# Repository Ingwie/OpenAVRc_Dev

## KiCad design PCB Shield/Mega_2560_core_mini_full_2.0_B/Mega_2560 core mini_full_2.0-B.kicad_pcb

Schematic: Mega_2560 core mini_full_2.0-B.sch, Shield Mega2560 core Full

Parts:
C1, C2, C3, C5: 47nF; C_1206
C4, C6, C7, C9, C11, C16, C17, C26, C27, C29, C31, C32, C33, C34, C38: 100nF; C_1206
C28: 47µF; CP_Elec_6.3x5.3
C42: 6.8nF; C_1206
C43, C44, C45, C46: 4.7nF; C_1206
D1, D2, D6: MBR0520; D_SOD-123
P1: 2560-core; Connectors-2560-core
P2: Clock; Pin_Header_Straight_1x04_Pitch2.54mm
P3: Option; Pin_Header_Straight_1x04_Pitch2.54mm
P4: Potentiometre; Pin_Header_Straight_2x05_Pitch2.54mm
P5: Vibreur; Pin_Header_Straight_1x02_Pitch2.54mm
P6: Micro_sd; Pin_Header_Straight_1x06_Pitch2.54mm
P7: Option; Pin_Header_Straight_1x06_Pitch2.54mm
P8: Audio; Pin_Header_Straight_1x05_Pitch2.54mm
P9: SPI; Pin_Header_Straight_2x03_Pitch2.54mm
P10: SPI_libre; Pin_Header_Straight_1x03_Pitch2.54mm
P11: Trim; Pin_Header_Straight_2x05_Pitch2.54mm
P12: Stick_left; Pin_Header_Straight_1x04_Pitch2.54mm
P13: Stick_right; Pin_Header_Straight_1x04_Pitch2.54mm
P14: Switch; Pin_Header_Straight_2x05_Pitch2.54mm
P15: LCD_I2C; Pin_Header_Straight_1x04_Pitch2.54mm
P16: LCD; Pin_Header_Straight_2x10_Pitch2.54mm
P17: Battery LIPO; Pin_Header_Straight_1x02_Pitch2.54mm
P18: Ecolage; Pin_Header_Straight_1x02_Pitch2.54mm
P19: Module_TX; Pin_Header_Straight_2x04_Pitch2.54mm
P20: Module_RS232/TTL; Con_RS232_TTL
P21: Sw_power; Pin_Header_Straight_1x02_Pitch2.54mm
P22: CONN_JQ6500_28P_mini; connector_mini-JQ6500-28P
P23: Rot_1; Pin_Header_Straight_1x04_Pitch2.54mm
P24: Rot_2; Pin_Header_Straight_1x04_Pitch2.54mm
P25: Key_select_menu_ESC; Pin_Header_Straight_2x04_Pitch2.54mm
P26: LCD_Vcc_select; Pin_Header_Straight_1x03_Pitch2.54mm
R1, R2: 22K; R_1206
R3: 18K; R_1206
R4: 1K; R_1206
R5, R6: 10K; R_1206
R7: 500; R_1206
R8: 200; R_1206
R9: 220; R_1206
R11, R12, R13, R14: 100K; R_1206
R16: 2.7K; R_1206
R17: 5.1K; R_1206
R18, R19, R22, R23: 5.1k; R_1206
R24, R25: 33K; R_1206
R26, R29, R32, R35: 47K; R_1206
R27, R30, R33, R36: POT_100k; Potentiometer_Trimmer_Bourns_3296W
R28, R31, R34, R37: 270K; R_1206
RV1: 200K; Potentiometer_Triwood_RM-065
RV2, RV3, RV4, RV5: POT_100k; Potentiometer_Bourns_3296W_3-8Zoll_Inline_ScrewUp
RV6: 120; Potentiometer_Trimmer_Bourns_3266W
SW1: Inter_HF
SW3: Power switch
U1: 4066; SOP14
U2, U3: TLP290; SOP4
U4: L4941; TO-220
U5: LD1117S33TR; SOT-223
U6: MCP604-I/SL; SOP14
W1, W2, W3, W4: TEST_2P; TESTPT

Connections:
+BATT: D6.2 (A), P19.1, P21.1, R7.1, R17.2
/Isp_rst: P1.RESE (P75), P9.5
/Key_DOWN: P1.49 (P29), P25.4
/Key_ESC: P1.44 (P34), P25.7
/Key_LEFT: P1.46 (P32), P25.5
/Key_MENU: P1.45 (P33), P25.8
/Key_RIGHT: P1.47 (P31), P25.6
/Key_UP: P1.48 (P30), P25.3
/LCD_VCC: P15.2, P16.3, P26.2
/Lcd_A0: P1.D32 (P85), P16.16
/Lcd_bla: P1.D35 (P88), RV6.1
/Lcd_cs: P1.D34 (P87), P16.20
/Lcd_db0: P1.D22 (P74), P16.6
/Lcd_db1: P1.D23 (P71), P16.7
/Lcd_db2: P1.D24 (P72), P16.8
/Lcd_db3: P1.D25 (P69), P16.9
/Lcd_db4: P1.D26 (P70), P16.10
/Lcd_db5: P1.D27 (P67), P16.11
/Lcd_db6: P1.D28 (P68), P16.12
/Lcd_db7: P1.D29 (P65), P16.13
/Lcd_e: P1.D30 (P83), P16.14
/Lcd_r/w: P1.D31 (P84), P16.15
/Lcd_rst: P1.D33 (P86), P16.17
/Lcd_vo: P16.4, RV1.2
/Microsd_CS: P1.53 (P24), P6.1, P7.1
/Miso: P1.MISO (P79), P6.4, P7.4, P9.1
/Mosi: P1.MOSI (P78), P6.3, P7.3, P9.4
/PH2: P1.PH2 (P19), P10.1
/PPM_TX_OUT: D2.1 (K), P19.4
/PPM_in: P1.PE7 (P10), U1.11 (I/O)
/PPM_out: D2.2 (A), P1.PW12 (P27), U1.8 (I/O)
/Pot_1: P1.A12 (P55), P4.6
/Pot_2: P1.A13 (P58), P4.2
/Pot_3: P1.A14 (P57), P4.4
/RXD2: P1.D17 (P14), P10.3
/Rot_1A: C29.1, P1.PWD2 (P7), P23.3
/Rot_1B: C27.1, P1.PWD3 (P8), P23.2, R18.2
/Rot_1push: C26.1, P1.D15 (P12), P23.1, R19.2
/Rot_2A: C34.1, P1.D19 (P16), P24.3
/Rot_2B: C33.1, P1.D18 (P15), P24.2, R22.2
/Rot_2push: C32.1, P1.D14 (P11), P24.1, R23.2
/Sck: P1.SCK (P77), P6.2, P7.2, P9.3
/Scl: P1.D21 (P18), P2.1, P3.1, P15.4
/Sda: P1.D20 (P17), P2.2, P3.2, P15.3
/Sim_control: P1.PW11 (P26), U1.5 (ON), U1.13 (ON)
/Stick_LH: C45.1, P1.A11 (P56), R33.2, R33.3, U6.8, W3.1
/Stick_LHcon: C9.2, P12.2, R32.2, W3.2
/Stick_LV: C46.1, P1.A9 (P54), R36.2, R36.3, U6.14, W4.1
/Stick_LVcon: C11.2, P12.3, R35.2, W4.2
/Stick_RH: C43.1, P1.A8 (P51), R27.2, R27.3, U6.1, W1.1
/Stick_RHcon: C16.2, P13.2, R26.2, W1.2
/Stick_RV: C44.1, P1.A10 (P53), R30.2, R30.3, U6.7, W2.1
/Stick_RVcon: C17.2, P13.3, R29.2, W2.2
/Sw_ailDR: P1.D38 (P93), P14.5
/Sw_eleDR: P1.43 (P35), P14.7
/Sw_gear: P1.D40 (P91), P14.4
/Sw_id1: P1.D37 (P90), P14.1
/Sw_id2: P1.D36 (P89), P14.2
/Sw_rudDR: P1.D41 (P92), P14.3
/Sw_thcut: P1.D39 (P66), P14.6
/Sw_turn: P1.42 (P36), P14.8
/TXD2: P1.D16 (P13), P10.2
/Tele_RX: P1.RXD (P4), U3.3
/Tele_TX: P1.TXD (P5), U2.4
/Trim_LH->: P1.A6 (P49), P11.1
/Trim_LH<-: P1.A7 (P52), P11.2
/Trim_LV->: P1.A4 (P47), P11.7
/Trim_LV<-: P1.A5 (P50), P11.4
/Trim_RH->: P1.A0 (P43), P11.5
/Trim_RH<-: P1.A1 (P46), P11.6
/Trim_RV->: P1.A2 (P45), P11.8
/Trim_RV<-: P1.A3 (P48), P11.3
/U_batt: P1.A15 (P60), R16.2, R17.1
/Vibreur: P1.PJ7 (P73), R9.2
/audio_left_in: P1.PWD6 (P20), R1.2
/audio_right_in: P22.DACL (P16), R2.2
/core_pw10: P1.PW10 (P25), R3.1
/core_pw13: P1.PW13 (P28), R4.1
unnamed: C28.1, D6.1 (K), U4.1 (IN)
unnamed 79: C38.1, P26.1, U5.2 (VO); also elsewhere on the board
unnamed: C42.1, R24.2, R25.1, U6.3 (+), U6.5 (+), U6.10 (+), U6.12 (+)
unnamed: C43.2, R11.2, R26.1, R28.1, U6.2 (-)
unnamed: C44.2, R12.2, R29.1, R31.1, U6.6 (-)
unnamed: C45.2, R13.2, R32.1, R34.1, U6.9 (-)
unnamed: C46.2, R14.2, R35.1, R37.1, U6.13 (-)
unnamed: D1.1 (K), P5.1, R9.1
unnamed: P8.1, R1.1
unnamed: P8.2, R2.1
unnamed: P16.5, RV1.3
unnamed: P16.18, RV6.2
unnamed: P17.2, P21.2
unnamed: P18.1, R8.1
unnamed: P19.2, P19.3
unnamed: P20.3, U2.3
unnamed: P22.BUSY (P20), R3.2
unnamed: P22.RX (P18), R4.2
unnamed: R5.2, U1.2 (O/I), U1.6 (ON)
unnamed: R6.2, U1.3 (O/I), U1.12 (ON)
unnamed: R7.2, U2.1, U3.1
unnamed: R8.2, U1.9 (O/I), U1.10 (O/I)
unnamed: R11.1, R27.1
unnamed: R12.1, R30.1
unnamed: R13.1, R33.1
unnamed: R14.1, R36.1
unnamed: R28.2, RV2.2
unnamed: R31.2, RV3.2
unnamed: R34.2, RV4.2
unnamed: R37.2, RV5.2

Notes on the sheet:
+3.3V
+5V
Isolation Module TTL
Power Management
PPM Management
Stick control
Option si utilisation du 3.3V dans le montage
Option Amplification des sticks (Fonctionne sans)
Option si utilisation de la télémètrie
Alim module

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
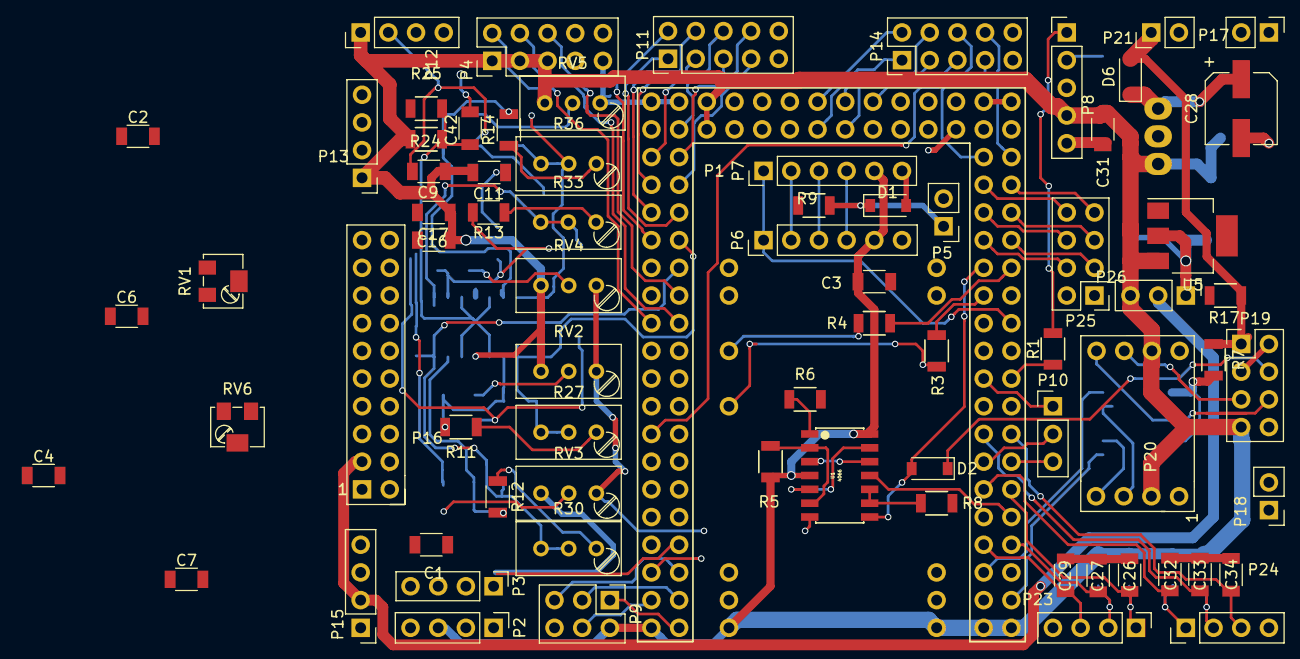
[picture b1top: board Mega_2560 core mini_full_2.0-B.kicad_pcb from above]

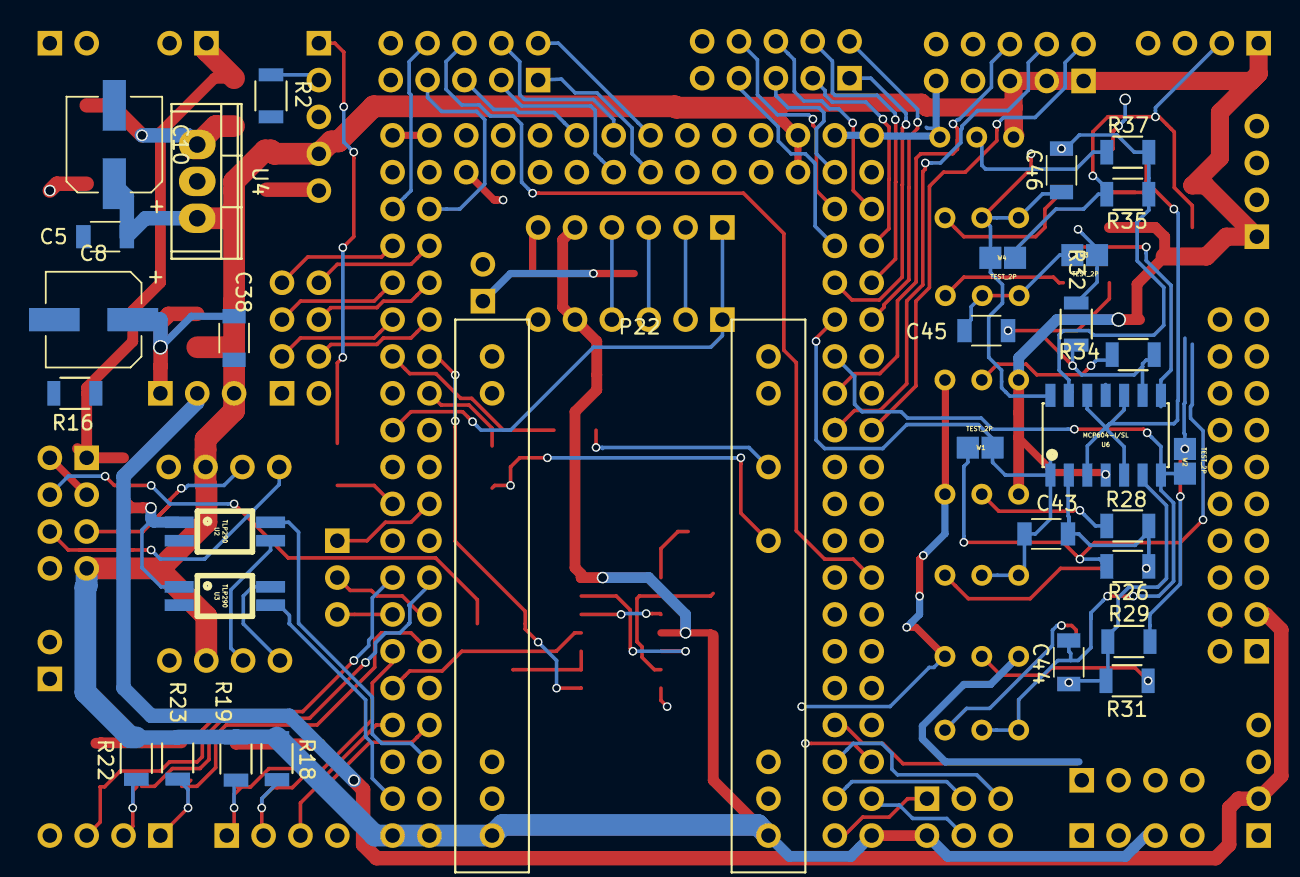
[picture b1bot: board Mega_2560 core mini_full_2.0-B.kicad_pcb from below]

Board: 2 copper layers, 105 parts (31 on the bottom side), 113 nets.

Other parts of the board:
C8, C10: 47µF; CP_Elec_6.3x5.3

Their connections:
unnamed 79: C8.1; also elsewhere on the board

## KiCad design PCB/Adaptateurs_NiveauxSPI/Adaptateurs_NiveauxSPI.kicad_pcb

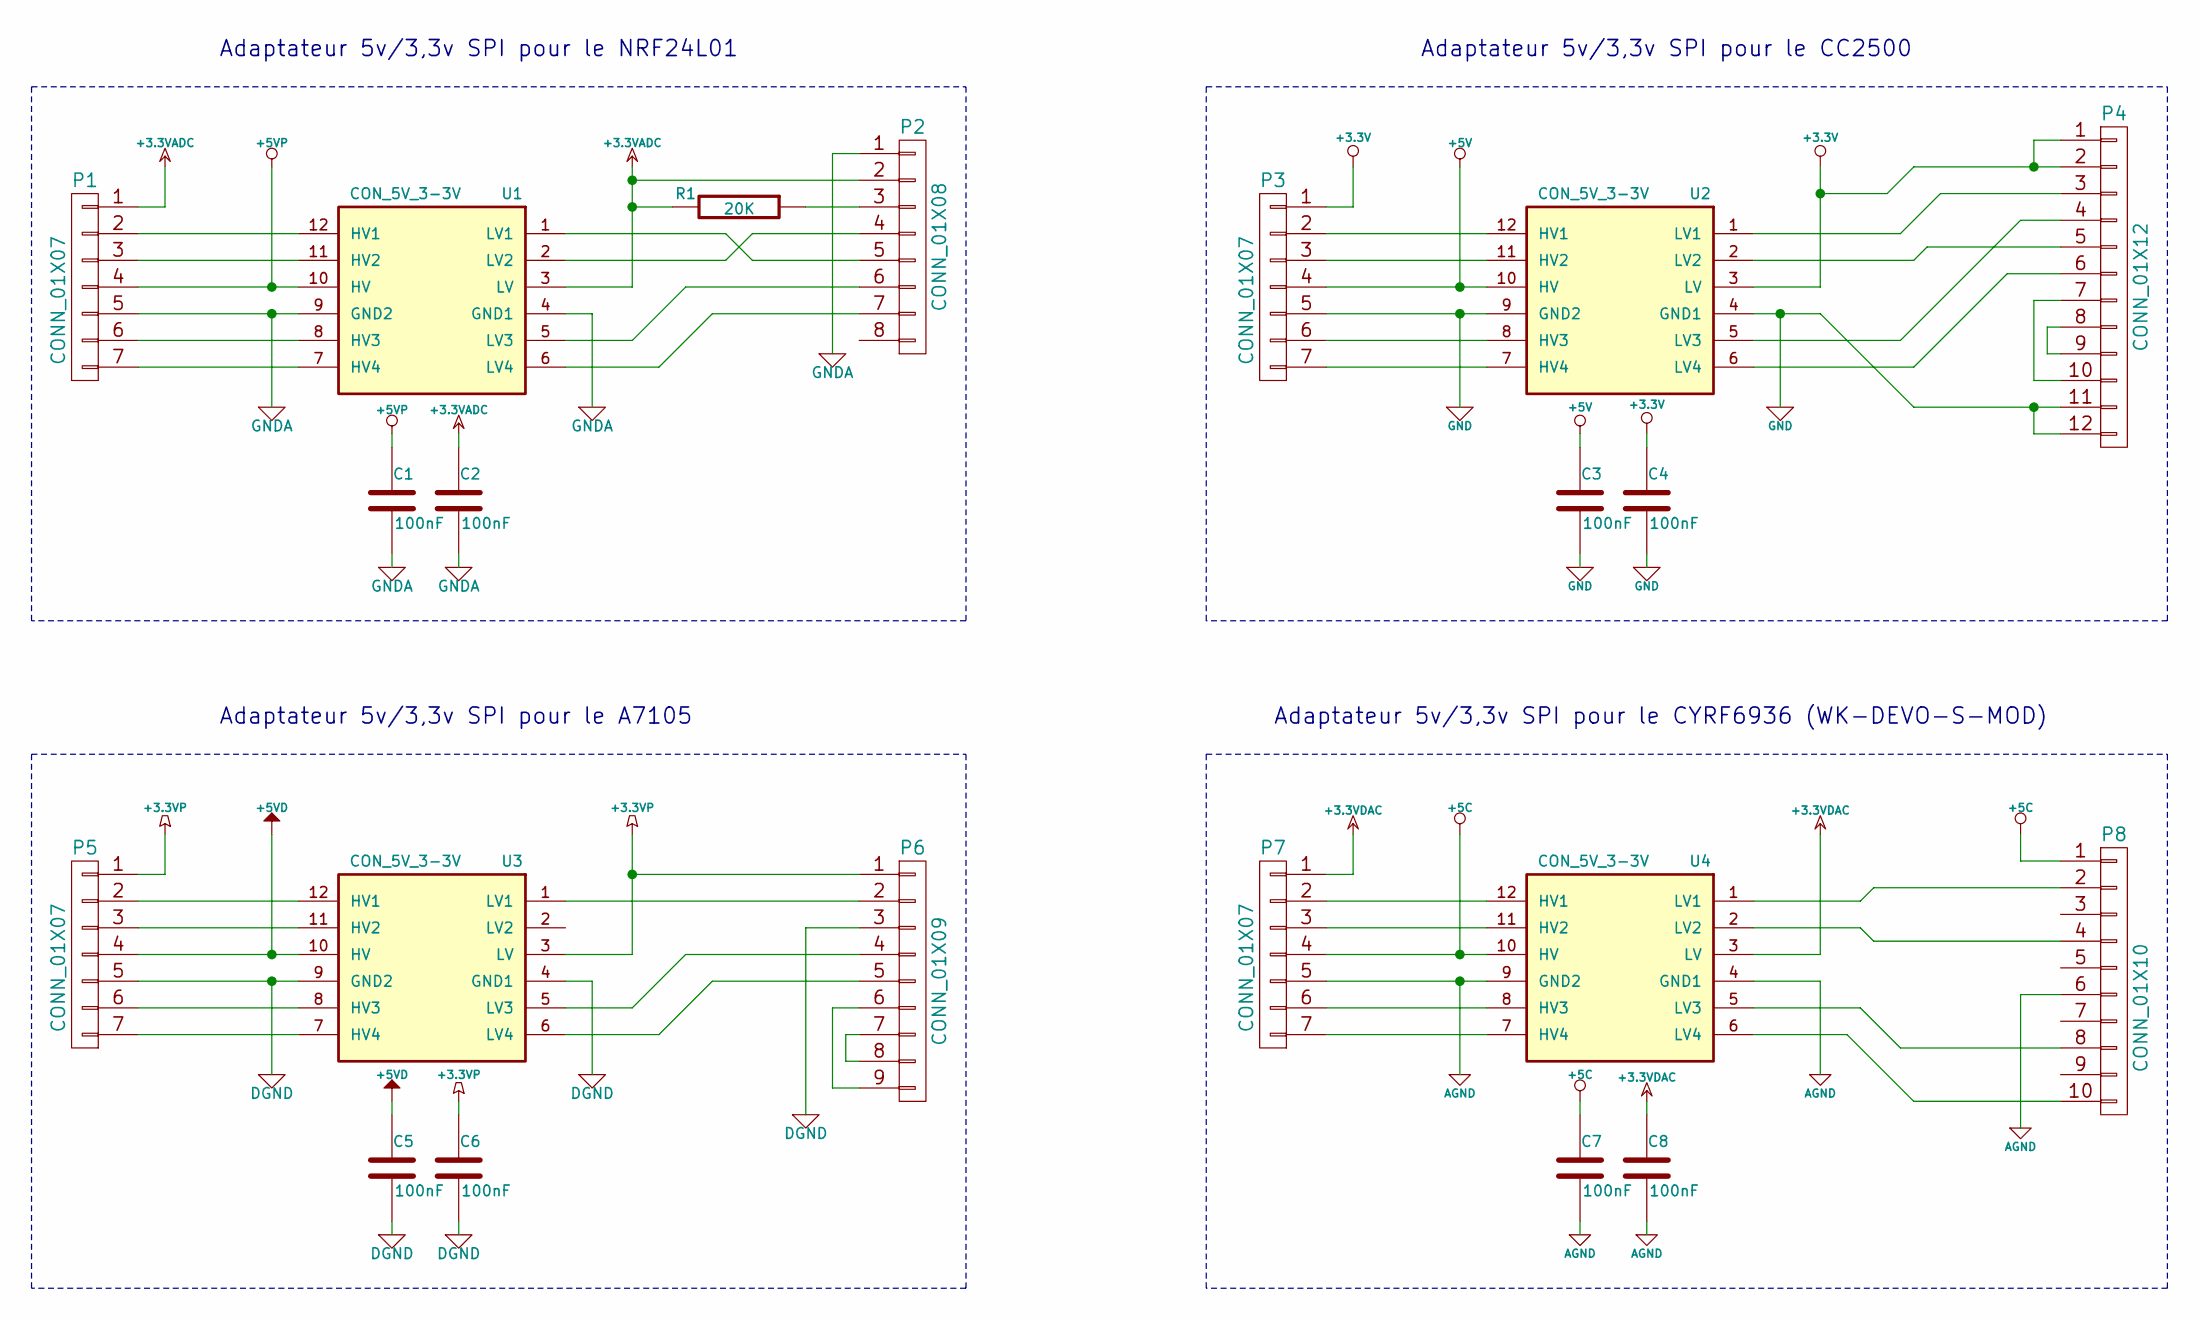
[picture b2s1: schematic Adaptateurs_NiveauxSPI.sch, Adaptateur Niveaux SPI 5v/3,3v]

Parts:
C1, C2, C3, C4, C5, C6, C7, C8: 100nF; C_1206
P1, P3, P5, P7: CONN_01X07; Pin_Header_Straight_1x07_Pitch2.54mm
P2: CONN_01X08; Pin_Header_Straight_2x04_Pitch2.54mm
P4: CONN_01X12; Pin_Header_Straight_2x06_Pitch2.54mm
P6: CONN_01X09; Pin_Header_Straight_1x09_Pitch2.54mm
P8: CONN_01X10; Pin_Header_Straight_2x05_Pitch2.54mm
R1: 20K; R_1206
U1, U2, U3, U4: CON_5V_3-3V; Level_Convertissor_W10.16mm

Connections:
+3.3V: C4.1, P3.1, P4.1, P4.2, U2.3 (LV)
+3.3VADC: C2.1, P1.1, P2.2, R1.2, U1.3 (LV)
+3.3VDAC: C8.1, P7.1, U4.3 (LV)
+3.3VP: C6.1, P5.1, P6.1, U3.3 (LV)
+5C: C7.1, P7.4, P8.1, U4.10 (HV)
+5V: C3.1, P3.4, U2.10 (HV)
+5VD: C5.1, P5.4, U3.10 (HV)
+5VP: C1.1, P1.4, U1.10 (HV)
AGND: C7.2, C8.2, P7.5, P8.6, U4.4 (GND1), U4.9 (GND2)
DGND: C5.2, C6.2, P5.5, P6.3, U3.4 (GND1), U3.9 (GND2)
GND: C3.2, C4.2, P3.5, P4.11, P4.12, U2.4 (GND1), U2.9 (GND2)
GNDA: C1.2, C2.2, P1.5, P2.1, U1.4 (GND1), U1.9 (GND2)
unnamed: P1.2, U1.12 (HV1)
unnamed: P1.3, U1.11 (HV2)
unnamed: P1.6, U1.8 (HV3)
unnamed: P1.7, U1.7 (HV4)
unnamed: P2.3, R1.1
unnamed: P2.4, U1.2 (LV2)
unnamed: P2.5, U1.1 (LV1)
unnamed: P2.6, U1.5 (LV3)
unnamed: P2.7, U1.6 (LV4)
unnamed: P3.2, U2.12 (HV1)
unnamed: P3.3, U2.11 (HV2)
unnamed: P3.6, U2.8 (HV3)
unnamed: P3.7, U2.7 (HV4)
unnamed: P4.3, U2.1 (LV1)
unnamed: P4.4, U2.5 (LV3)
unnamed: P4.5, U2.2 (LV2)
unnamed: P4.6, U2.6 (LV4)
unnamed: P4.8, P4.9
unnamed: P4.7, P4.10
unnamed: P5.2, U3.12 (HV1)
unnamed: P5.3, U3.11 (HV2)
unnamed: P5.6, U3.8 (HV3)
unnamed: P5.7, U3.7 (HV4)
unnamed: P6.2, U3.1 (LV1)
unnamed: P6.4, U3.5 (LV3)
unnamed: P6.5, U3.6 (LV4)
unnamed: P6.6, P6.9
unnamed: P6.7, P6.8
unnamed: P7.2, U4.12 (HV1)
unnamed: P7.3, U4.11 (HV2)
unnamed: P7.6, U4.8 (HV3)
unnamed: P7.7, U4.7 (HV4)
unnamed: P8.2, U4.1 (LV1)
unnamed: P8.4, U4.2 (LV2)
unnamed: P8.8, U4.5 (LV3)
unnamed: P8.10, U4.6 (LV4)

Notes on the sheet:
Adaptateur 5v/3,3v SPI pour le NRF24L01
Adaptateur 5v/3,3v SPI pour le CC2500
Adaptateur 5v/3,3v SPI pour le A7105
Adaptateur 5v/3,3v SPI pour le CYRF6936 (WK-DEVO-S-MOD)

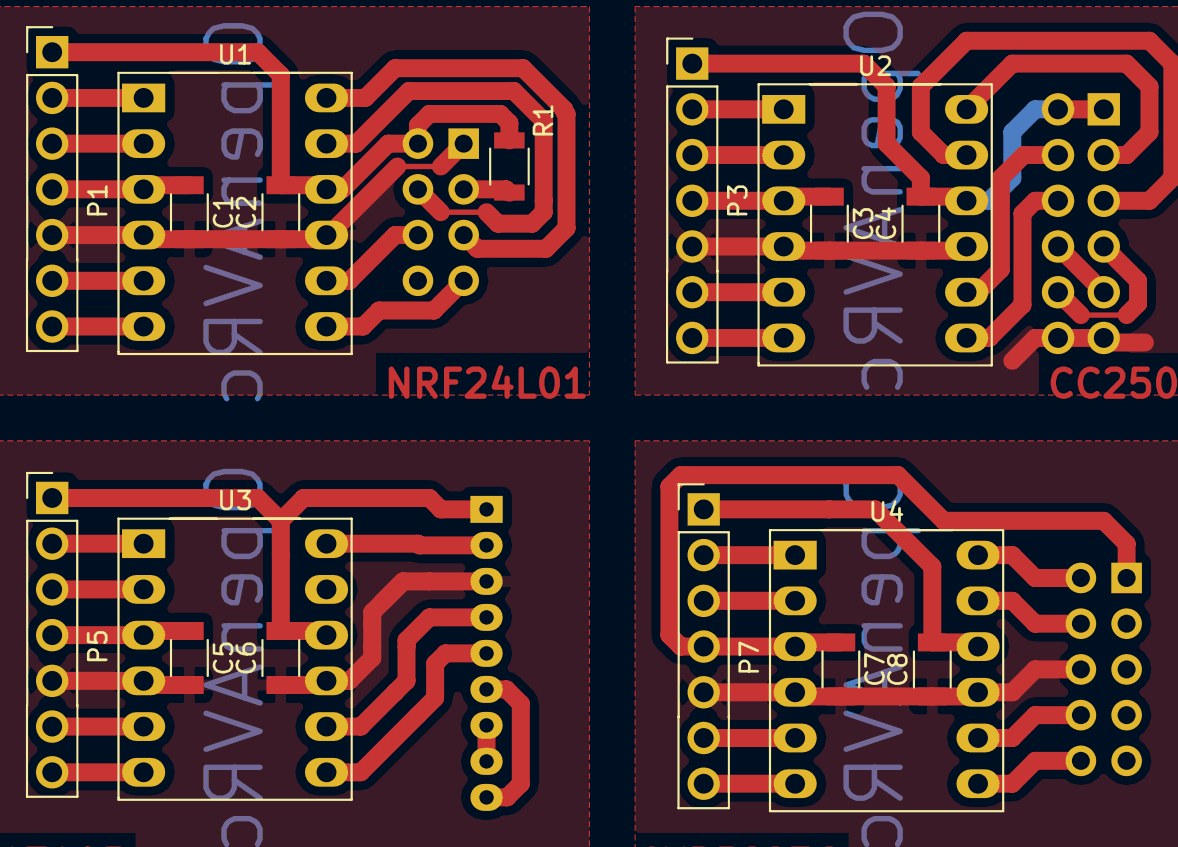
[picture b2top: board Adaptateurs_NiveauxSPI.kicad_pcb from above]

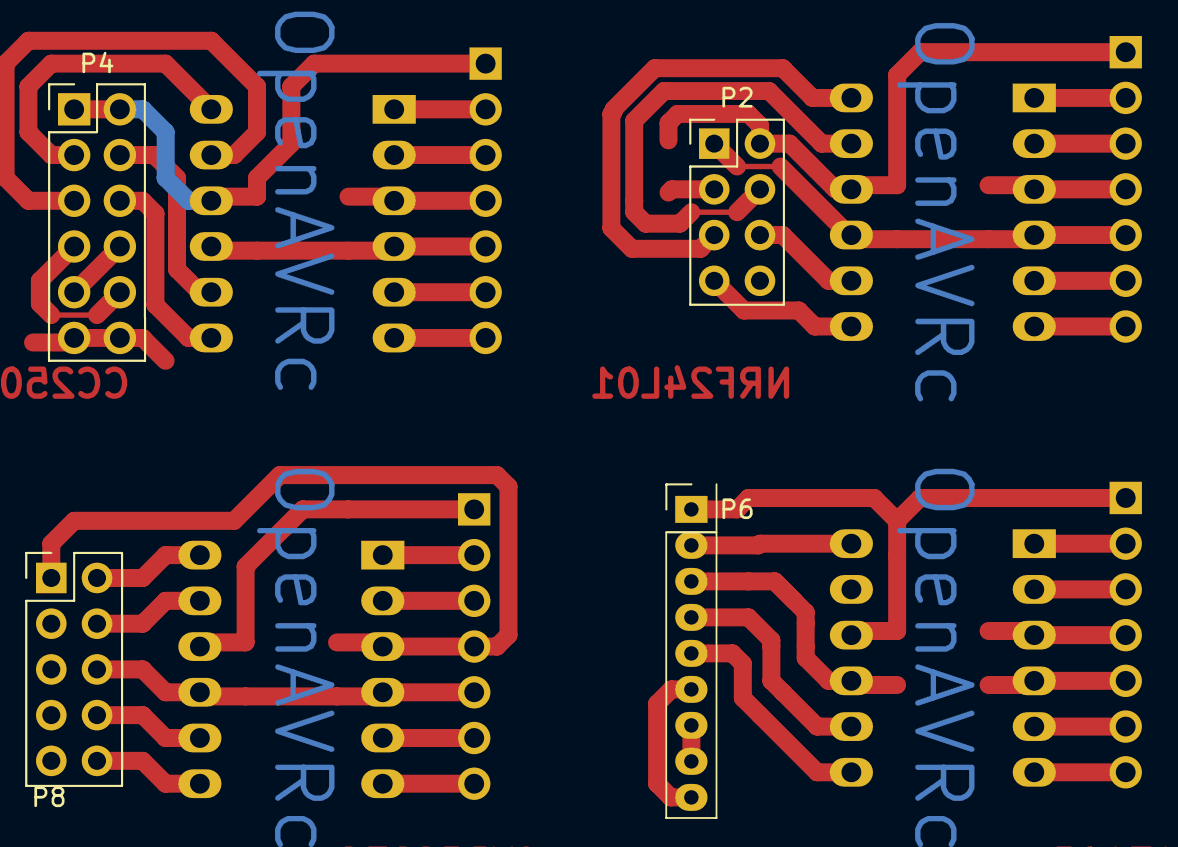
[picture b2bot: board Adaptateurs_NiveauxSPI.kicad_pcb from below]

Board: 2 copper layers, 21 parts (4 on the bottom side), 48 nets.

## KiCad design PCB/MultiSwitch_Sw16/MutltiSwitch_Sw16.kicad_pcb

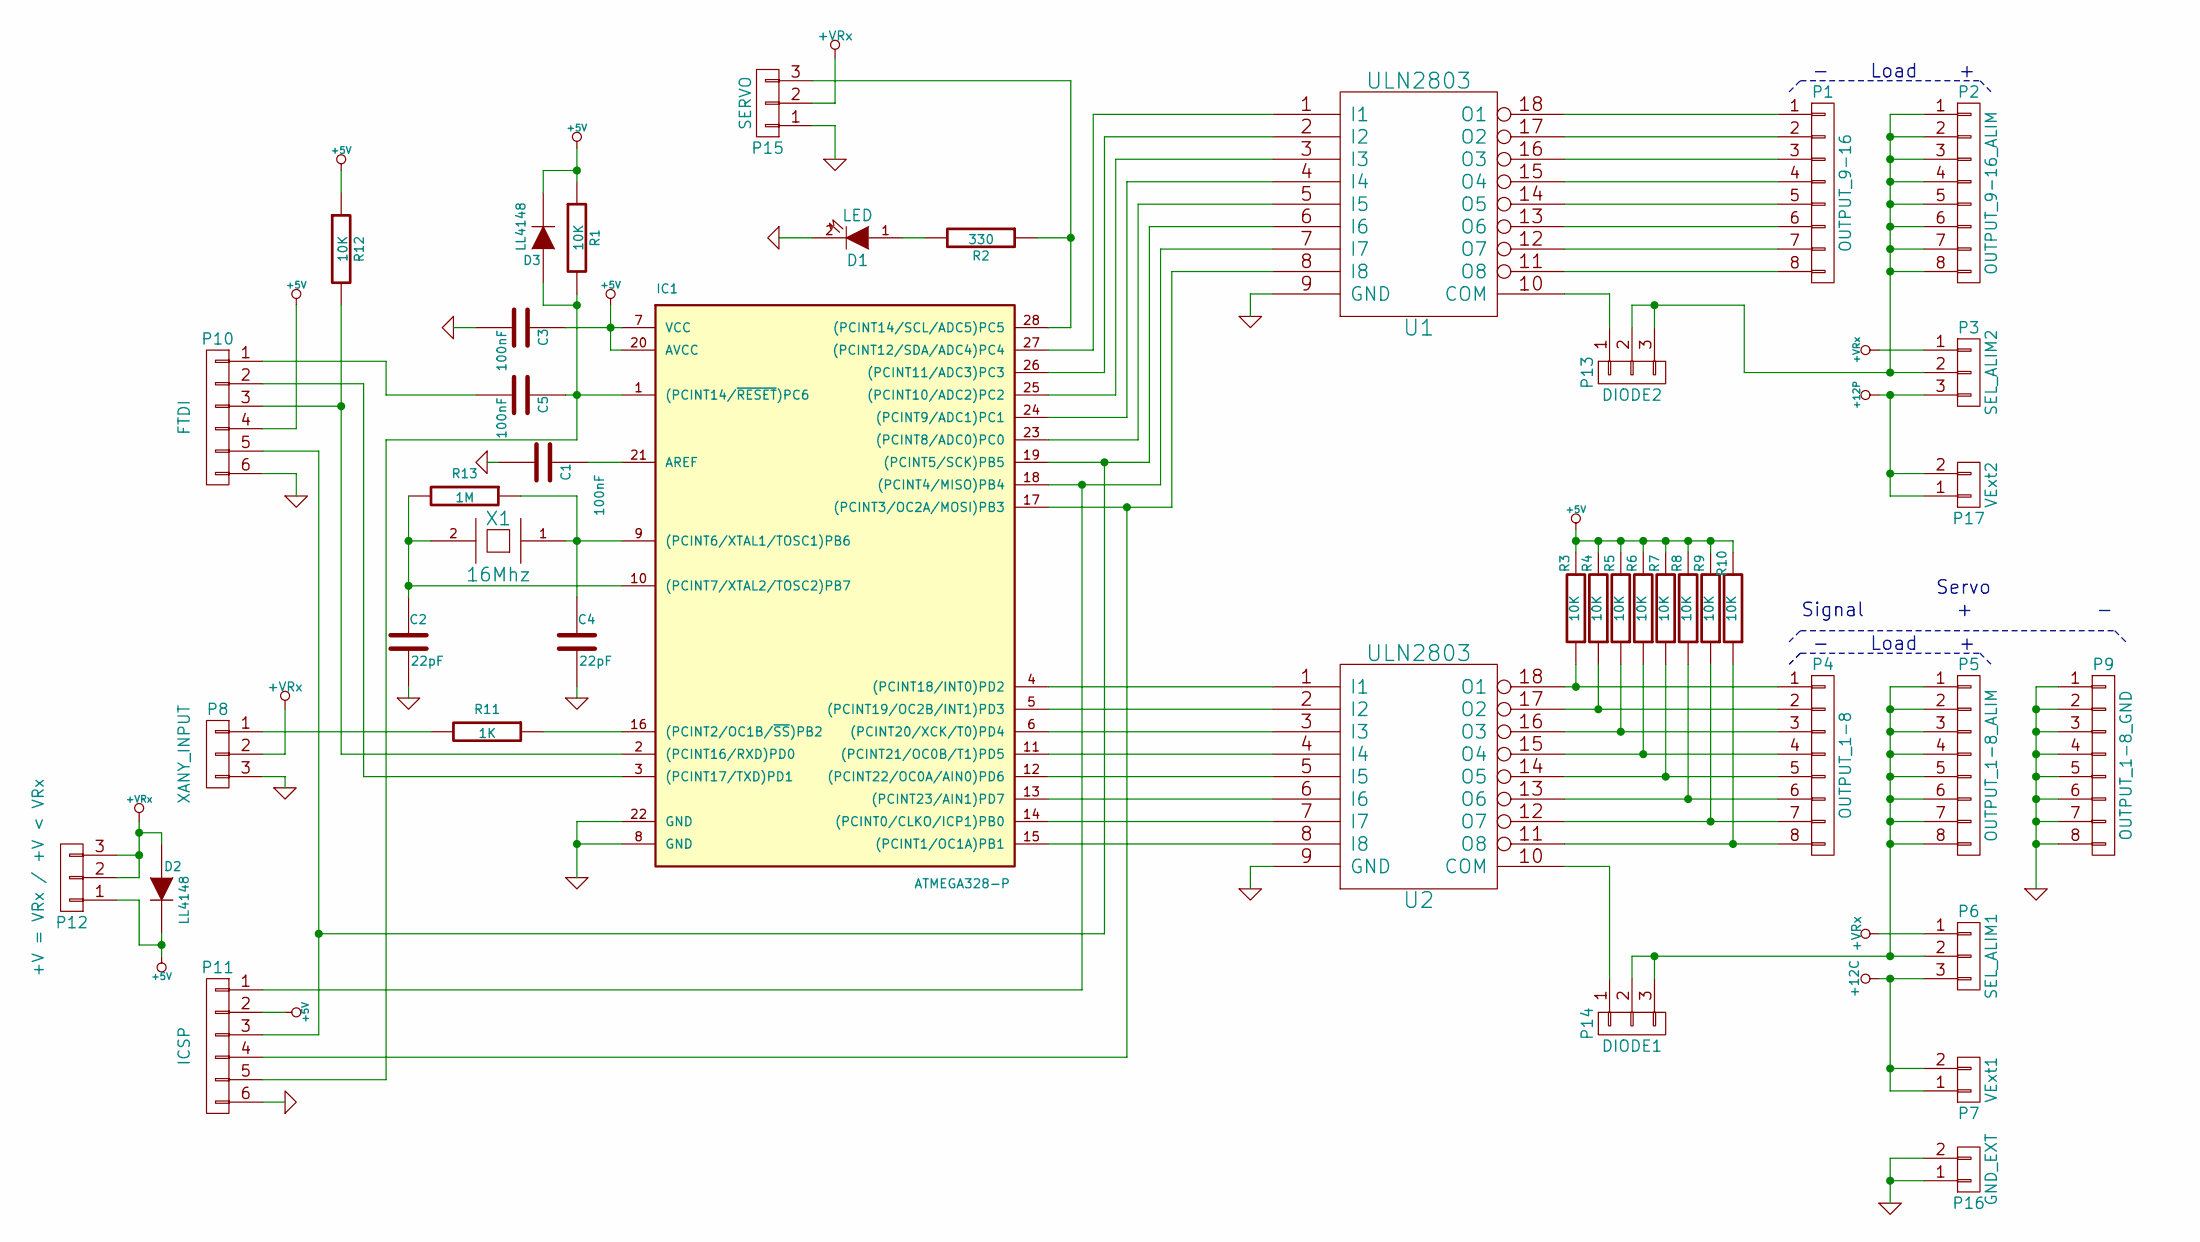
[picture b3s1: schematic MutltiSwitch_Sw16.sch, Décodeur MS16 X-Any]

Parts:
C1, C3, C5: 100nF; C_1206
C2, C4: 22pF; C_1206
D1: LED; LED_1206
D2, D3: LL4148; D_SOD-123
IC1: ATMEGA328-P; DIP-28_W7.62mm_LongPads
P1: OUTPUT_9-16; Pin_Header_Straight_1x08_Pitch2.54mm
P2: OUTPUT_9-16_ALIM; Pin_Header_Straight_1x08_Pitch2.54mm
P3: SEL_ALIM2; Pin_Header_Straight_1x03_Pitch2.54mm
P4: OUTPUT_1-8; Pin_Header_Straight_1x08_Pitch2.54mm
P5: OUTPUT_1-8_ALIM; Pin_Header_Straight_1x08_Pitch2.54mm
P6: SEL_ALIM1; Pin_Header_Straight_1x03_Pitch2.54mm
P7: VExt1; Faston_V-5_08
P8: XANY_INPUT; Pin_Header_Straight_1x03_Pitch2.54mm
P9: OUTPUT_1-8_GND; Pin_Header_Straight_1x08_Pitch2.54mm
P10: FTDI; Pin_Header_Straight_2x03_Pitch2.54mm
P11: ICSP; Pin_Header_Straight_2x03_Pitch2.54mm
P12: +V = VRx / +V < VRx; Pin_Header_Straight_1x03_Pitch2.54mm
P13: DIODE2; Pin_Header_Straight_1x03_Pitch2.54mm
P14: DIODE1; Pin_Header_Straight_1x03_Pitch2.54mm
P15: SERVO
P16: GND_EXT; Faston_V-5_08
P17: VExt2; Faston_V-5_08
R1, R3, R4, R5, R6, R7, R8, R9, R10, R12: 10K; R_1206
R2: 330; R_1206
R11: 1K; R_1206
R13: 1M; R_1206
U1, U2: ULN2803; DIP-18_W7.62mm_LongPads
X1: 16Mhz; HC-39

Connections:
+5V: C3.1, D2.2 (K), D3.2 (K), IC1.7 (VCC), IC1.20 (AVCC), P10.4, P11.2, P12.1, R1.1, R3.2, R4.2, R5.2, R6.2, R7.2, R8.2, R9.2, R10.2, R12.1
+12C: P6.3, P7.1, P7.2
+12P: P3.3, P17.1, P17.2
+VRx: D2.1 (A), P3.1, P6.1, P8.2, P12.2, P12.3, P15.2
GND: C1.2, C2.2, C3.2, C4.2, D1.2 (K), IC1.8 (GND), IC1.22 (GND), P8.3, P9.1, P9.2, P9.3, P9.4, P9.5, P9.6, P9.7, P9.8, P10.6, P11.6, P15.1, P16.1, P16.2, U1.9 (GND), U2.9 (GND)
unnamed: C1.1, IC1.21 (AREF)
unnamed: C2.1, IC1.10 ((PCINT7/XTAL2/TOSC2)PB7), R13.2, X1.2
unnamed: C4.1, IC1.9 ((PCINT6/XTAL1/TOSC1)PB6), R13.1, X1.1
unnamed: C5.1, D3.1 (A), IC1.1 ((PCINT14/~RESET~)PC6), P11.5, R1.2
unnamed: C5.2, P10.1
unnamed: D1.1 (A), R2.2
unnamed: IC1.2 ((PCINT16/RXD)PD0), P10.3, R12.2
unnamed: IC1.3 ((PCINT17/TXD)PD1), P10.2
unnamed: IC1.4 ((PCINT18/INT0)PD2), U2.1 (I1)
unnamed: IC1.5 ((PCINT19/OC2B/INT1)PD3), U2.2 (I2)
unnamed: IC1.6 ((PCINT20/XCK/T0)PD4), U2.3 (I3)
unnamed: IC1.11 ((PCINT21/OC0B/T1)PD5), U2.4 (I4)
unnamed: IC1.12 ((PCINT22/OC0A/AIN0)PD6), U2.5 (I5)
unnamed: IC1.13 ((PCINT23/AIN1)PD7), U2.6 (I6)
unnamed: IC1.14 ((PCINT0/CLKO/ICP1)PB0), U2.7 (I7)
unnamed: IC1.15 ((PCINT1/OC1A)PB1), U2.8 (I8)
unnamed: IC1.16 ((PCINT2/OC1B/~SS~)PB2), R11.1
unnamed: IC1.17 ((PCINT3/OC2A/MOSI)PB3), P11.4, U1.8 (I8)
unnamed: IC1.18 ((PCINT4/MISO)PB4), P11.1, U1.7 (I7)
unnamed: IC1.19 ((PCINT5/SCK)PB5), P10.5, P11.3, U1.6 (I6)
unnamed: IC1.23 ((PCINT8/ADC0)PC0), U1.5 (I5)
unnamed: IC1.24 ((PCINT9/ADC1)PC1), U1.4 (I4)
unnamed: IC1.25 ((PCINT10/ADC2)PC2), U1.3 (I3)
unnamed: IC1.26 ((PCINT11/ADC3)PC3), U1.2 (I2)
unnamed: IC1.27 ((PCINT12/SDA/ADC4)PC4), U1.1 (I1)
unnamed: IC1.28 ((PCINT14/SCL/ADC5)PC5), P15.3, R2.1
unnamed: P1.1, U1.18 (O1)
unnamed: P1.2, U1.17 (O2)
unnamed: P1.3, U1.16 (O3)
unnamed: P1.4, U1.15 (O4)
unnamed: P1.5, U1.14 (O5)
unnamed: P1.6, U1.13 (O6)
unnamed: P1.7, U1.12 (O7)
unnamed: P1.8, U1.11 (O8)
unnamed: P4.1, R3.1, U2.18 (O1)
unnamed: P4.2, R4.1, U2.17 (O2)
unnamed: P4.3, R5.1, U2.16 (O3)
unnamed: P4.4, R6.1, U2.15 (O4)
unnamed: P4.5, R7.1, U2.14 (O5)
unnamed: P4.6, R8.1, U2.13 (O6)
unnamed: P4.7, R9.1, U2.12 (O7)
unnamed: P4.8, R10.1, U2.11 (O8)
unnamed: P8.1, R11.2
unnamed: P13.1, U1.10 (COM)
unnamed: P2.1, P2.2, P2.3, P2.4, P2.5, P2.6, P2.7, P2.8, P3.2, P13.2, P13.3
unnamed: P14.1, U2.10 (COM)
unnamed: P5.1, P5.2, P5.3, P5.4, P5.5, P5.6, P5.7, P5.8, P6.2, P14.2, P14.3

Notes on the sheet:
- Load +
Signal + -
Servo

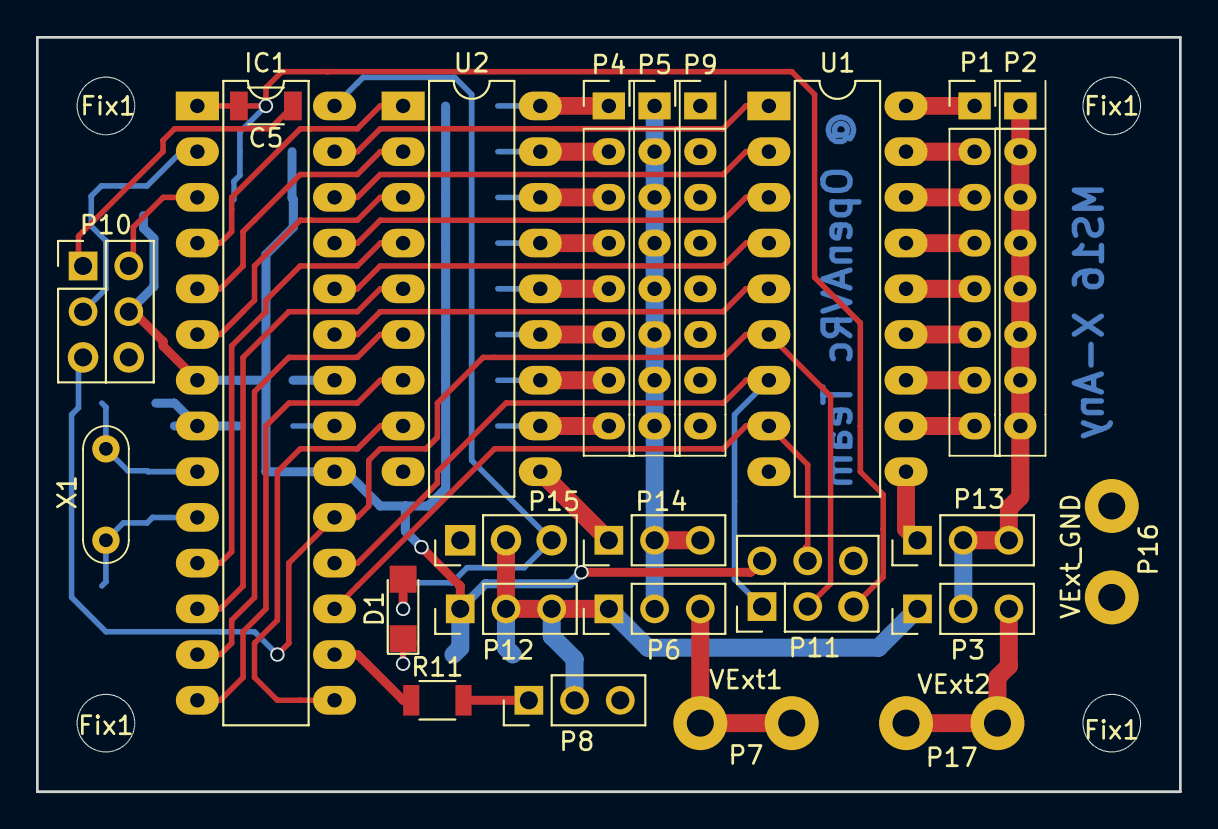
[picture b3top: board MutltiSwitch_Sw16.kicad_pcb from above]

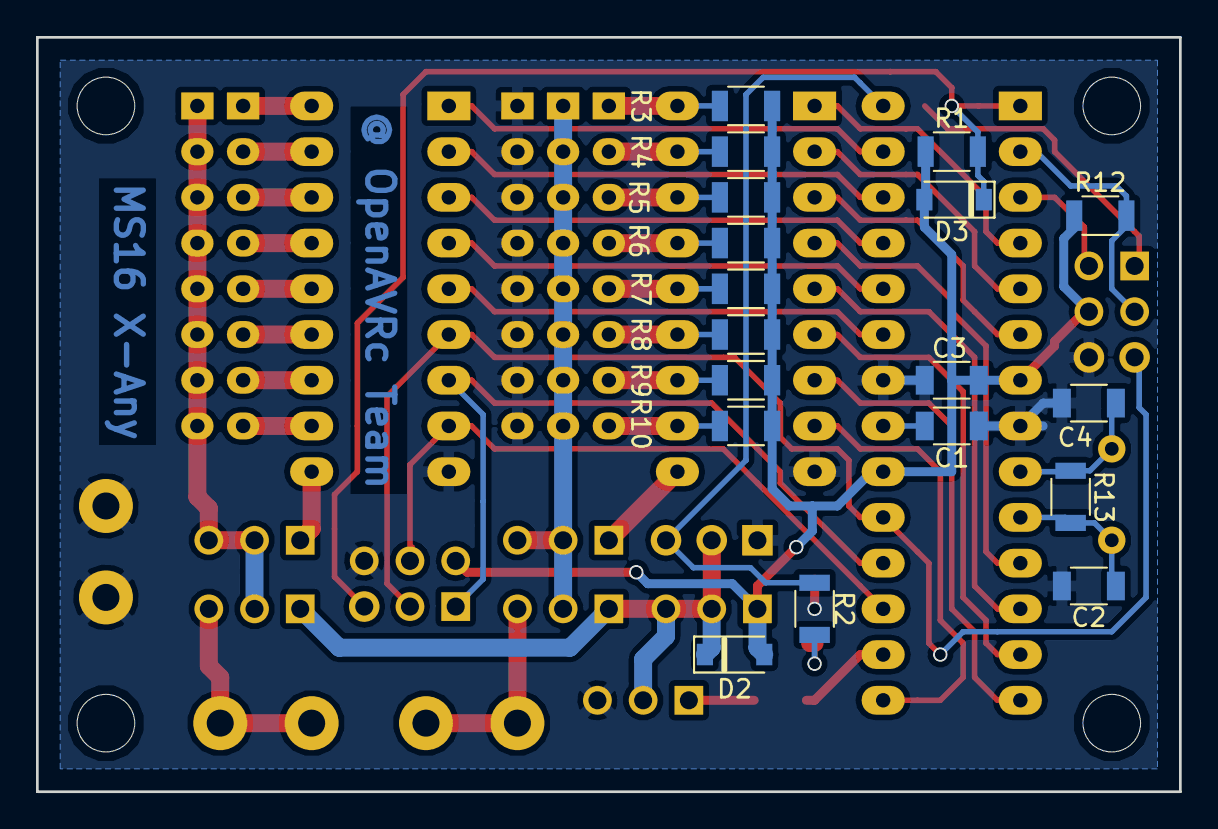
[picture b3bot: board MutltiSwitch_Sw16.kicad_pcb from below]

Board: 2 copper layers, 63.5 x 41.9 mm, 46 parts (18 on the bottom side), 52 nets.

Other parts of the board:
Fix1, Fix1#2, Fix1#3, Fix1#4: MountingHole_3.2mm_M3

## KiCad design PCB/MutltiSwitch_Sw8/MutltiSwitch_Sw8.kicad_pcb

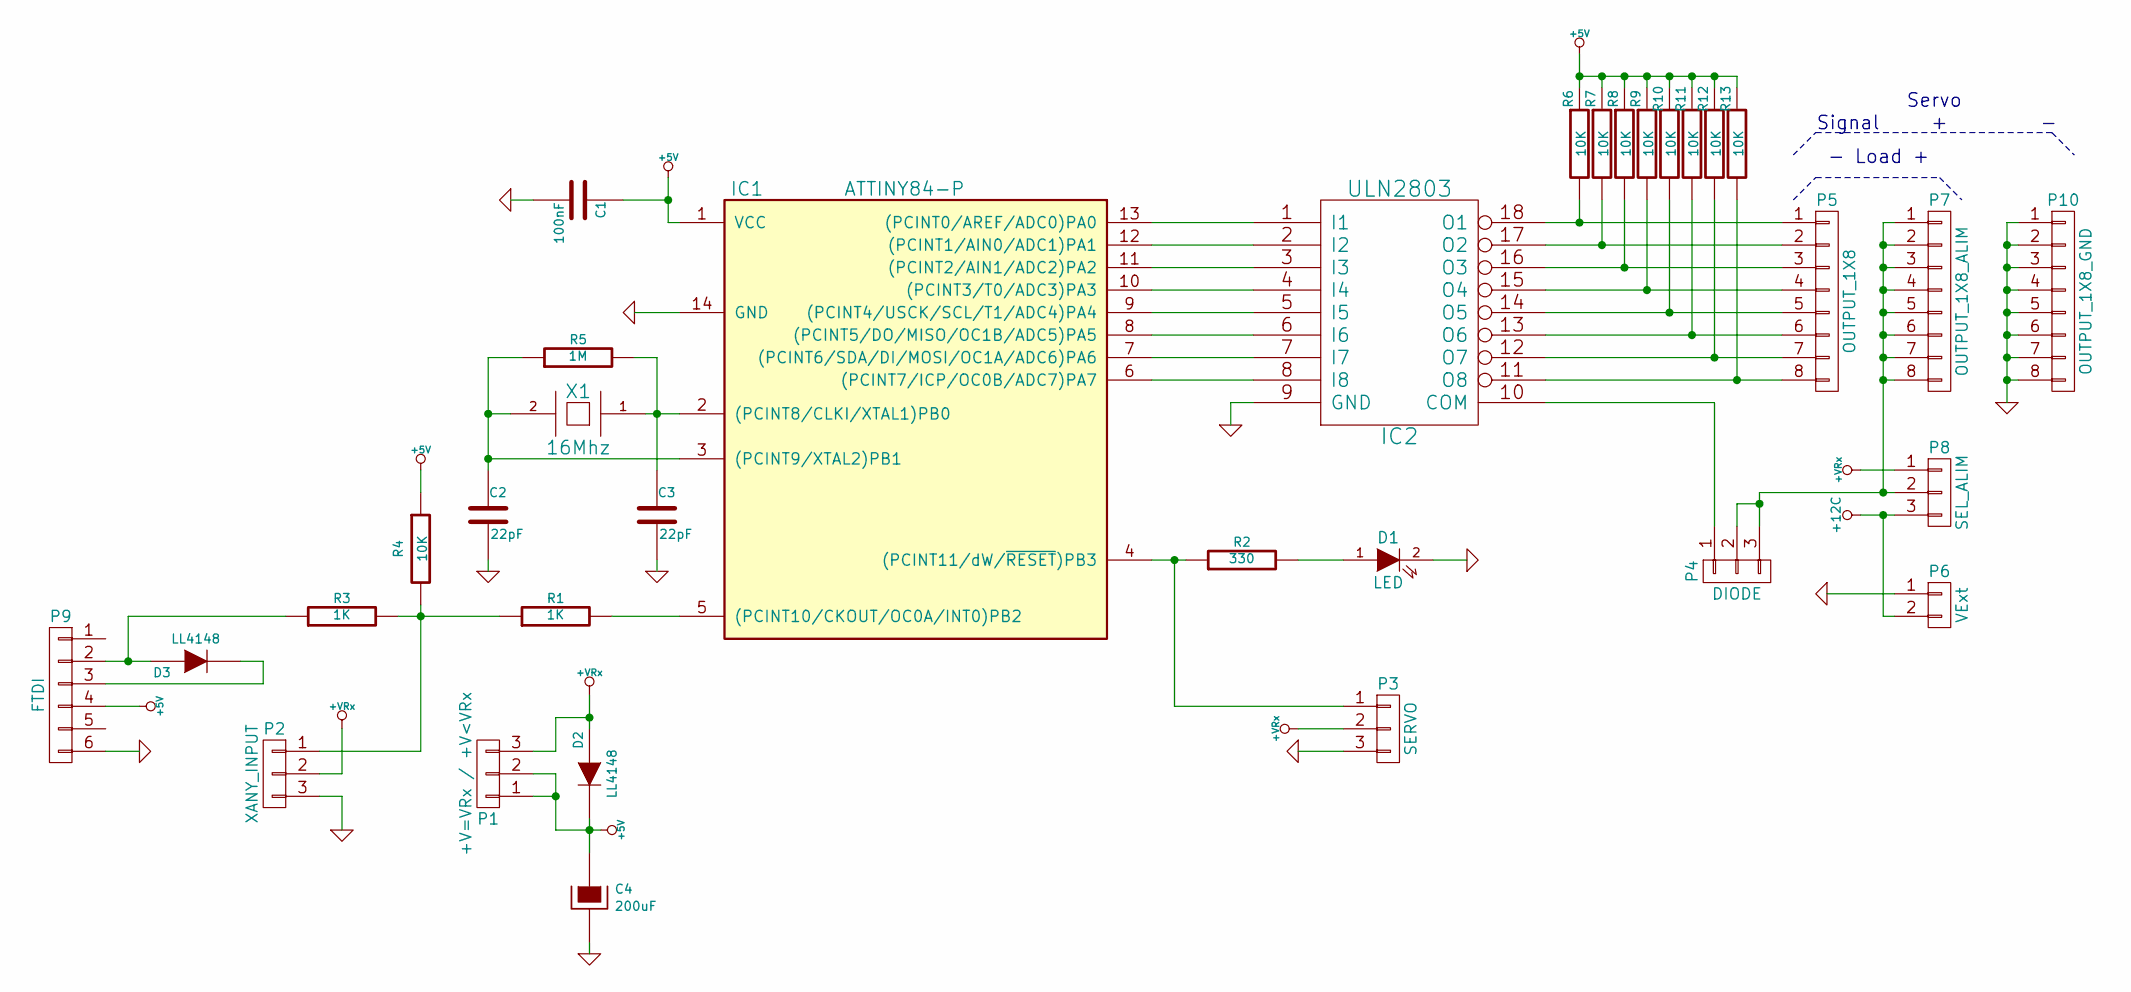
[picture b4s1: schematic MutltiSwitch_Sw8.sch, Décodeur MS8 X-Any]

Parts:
C1: 100nF; C_1206
C2, C3: 22pF; C_1206
C4: 200uF; CP_Tantalum_Case-D_EIA-7343-31_Hand
D1: LED; LED_1206
D2, D3: LL4148; D_SOD-123
IC1: ATTINY84-P; DIP-14_W7.62mm_LongPads
IC2: ULN2803; DIP-18_W7.62mm_LongPads
P1: +V=VRx / +V<VRx; Pin_Header_Straight_1x03_Pitch2.54mm
P2: XANY_INPUT; Pin_Header_Straight_1x03_Pitch2.54mm
P3: SERVO; Pin_Header_Straight_1x03_Pitch2.54mm
P4: DIODE; Pin_Header_Straight_1x03_Pitch2.54mm
P5: OUTPUT_1X8; Pin_Header_Straight_1x09_Pitch2.54mm
P6: VExt; Faston_V-5_08
P7: OUTPUT_1X8_ALIM; Pin_Header_Straight_1x09_Pitch2.54mm
P8: SEL_ALIM; Pin_Header_Straight_1x03_Pitch2.54mm
P9: FTDI; Pin_Header_Straight_2x03_Pitch2.54mm
P10: OUTPUT_1X8_GND; Pin_Header_Straight_1x09_Pitch2.54mm
R1, R3: 1K; R_1206
R2: 330; R_1206
R4, R6, R7, R8, R9, R10, R11, R12, R13: 10K; R_1206
R5: 1M; R_1206
X1: 16Mhz; HC-39

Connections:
+5V: C1.1, C4.1, D2.2 (K), IC1.1 (VCC), P1.1, P1.2, P9.4, R4.1, R6.1, R7.1, R8.1, R9.1, R10.1, R11.1, R12.1, R13.1
+12C: P6.2, P8.3
+VRx: D2.1 (A), P1.3, P2.2, P3.2, P8.1
GND: C1.2, C2.2, C3.2, C4.2, D1.2 (K), IC1.14 (GND), IC2.9 (GND), P2.3, P3.3, P6.1, P9.6, P10.1, P10.2, P10.3, P10.4, P10.5, P10.6, P10.7, P10.8
unnamed: C2.1, IC1.3 ((PCINT9/XTAL2)PB1), R5.1, X1.2
unnamed: C3.1, IC1.2 ((PCINT8/CLKI/XTAL1)PB0), R5.2, X1.1
unnamed: D1.1 (A), R2.2
unnamed: D3.1 (A), P9.2, R3.1
unnamed: D3.2 (K), P9.3
unnamed: IC1.4 ((PCINT11/dW/~RESET~)PB3), P3.1, R2.1
unnamed: IC1.5 ((PCINT10/CKOUT/OC0A/INT0)PB2), R1.2
unnamed: IC1.6 ((PCINT7/ICP/OC0B/ADC7)PA7), IC2.8 (I8)
unnamed: IC1.7 ((PCINT6/SDA/DI/MOSI/OC1A/ADC6)PA6), IC2.7 (I7)
unnamed: IC1.8 ((PCINT5/DO/MISO/OC1B/ADC5)PA5), IC2.6 (I6)
unnamed: IC1.9 ((PCINT4/USCK/SCL/T1/ADC4)PA4), IC2.5 (I5)
unnamed: IC1.10 ((PCINT3/T0/ADC3)PA3), IC2.4 (I4)
unnamed: IC1.11 ((PCINT2/AIN1/ADC2)PA2), IC2.3 (I3)
unnamed: IC1.12 ((PCINT1/AIN0/ADC1)PA1), IC2.2 (I2)
unnamed: IC1.13 ((PCINT0/AREF/ADC0)PA0), IC2.1 (I1)
unnamed: IC2.10 (COM), P4.1
unnamed: IC2.11 (O8), P5.8, R13.2
unnamed: IC2.12 (O7), P5.7, R12.2
unnamed: IC2.13 (O6), P5.6, R11.2
unnamed: IC2.14 (O5), P5.5, R10.2
unnamed: IC2.15 (O4), P5.4, R9.2
unnamed: IC2.16 (O3), P5.3, R8.2
unnamed: IC2.17 (O2), P5.2, R7.2
unnamed: IC2.18 (O1), P5.1, R6.2
unnamed: P2.1, R1.1, R3.2, R4.2
unnamed: P4.2, P4.3, P7.1, P7.2, P7.3, P7.4, P7.5, P7.6, P7.7, P7.8, P8.2

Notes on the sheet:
- Load +
Signal + -
Servo
